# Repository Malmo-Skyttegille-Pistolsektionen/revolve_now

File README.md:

<h1></h1>

Software for running timed shooting programs on a rotating target system, built
by and for Malmö Skyttegille Pistolsektionen.

An ESP32-S3 board turns the targets face-on and edge-on to a shooting program
and plays the spoken range commands over an amplifier. A React web app — served
by the board itself over WiFi — starts and stops programs, follows the run live
over Server-Sent Events, and manages the stored programs and audio.

## ⚠️ SAFETY WARNING — READ BEFORE INSTALLING OR OPERATING

**This device moves steel on a live firing range, and it moves it on a timer.**
A target turns because a program said it was time, not because it can see who
is in front of it. It has no idea anyone is downrange.

- **The range's own safety rules and range commands govern the line. This
  software governs nothing.** A program running is not a range that is hot; a
  program stopped is not a range that is safe.
- **NEVER go downrange because the web app says the run has finished.** Confirm
  a cease-fire the way your range already requires — verbally, with firearms
  cleared and benched.
- **NEVER leave the device powered while people are forward of the firing
  line** unless your club has decided that is safe and knows what the targets
  do at power-up.
- **A target turning can injure somebody standing next to it.** Keep clear of
  the mechanism whenever the device is powered.

The targets rest **shown** at boot, deliberately: a target that turns of its own
accord when a board is powered is the failure this project is most concerned
with. That resting state can be changed to suit a target system wired the other
way round, but only over a USB cable, never from the web app — see
[Expert mode](https://malmo-skyttegille-pistolsektionen.github.io/revolve_now/expert-mode/).

**Do not rely on this software to protect anyone.** It is a convenience for
running programs, not a safety device, and it has no interlock, no sensor, and
no way to know where people are.

**LIABILITY DISCLAIMER:** This project is provided as-is with absolutely no
warranty of any kind. The author(s) accept no responsibility or liability for
any injury, damage, or loss resulting from building, installing, modifying, or
operating this system. You build and use it entirely at your own risk.

---

## Documentation

Everything an operator needs is on the documentation site, in English and
Swedish (the language menu in the header switches):

- **[Operator documentation](https://malmo-skyttegille-pistolsektionen.github.io/revolve_now/)**
  — wiring, connecting, running a program, settings, and what the status LED is
  telling you. This is the one to send a club member.
- **[Program editor](https://malmo-skyttegille-pistolsektionen.github.io/revolve_now/editor/)**
  — write and edit programs in a browser with **no device attached**, then
  download the file or open a pull request against this repository. Also useful
  for reading a shipped program without a board in front of you.
- **[Hardware and wiring](https://malmo-skyttegille-pistolsektionen.github.io/revolve_now/hardware/)**
  — what a target system has to do to work, the DB9 pinout, and the transistor
  that does the switching.

## Installing

Releases ship a pre-built firmware image; you do not need a toolchain to put it
on a board. See
[Connecting](https://malmo-skyttegille-pistolsektionen.github.io/revolve_now/connecting/)
for getting the device onto your network afterwards, and
[Settings](https://malmo-skyttegille-pistolsektionen.github.io/revolve_now/settings/)
for adapting a stock image to your own board — the target pin, its polarity,
the audio and LED pins and the device's name are all configurable on the
device, without rebuilding it.

## Target systems

- **[Eigenbrod TP2](https://eigenbrod-schiessanlagen.de/en/products?tx_produkt_produkte%5Baction%5D=show&tx_produkt_produkte%5BL%5D=2&tx_produkt_produkte%5Bprodukt%5D=319&cHash=942340d5971be0a0ac3d26ff3c257c0b)**
  — what this was built against and what it runs on.

Nothing in the firmware is specific to that system. The board speaks no
proprietary protocol to the targets: it closes and opens **one circuit**, and
the target system's own electronics do the rest. Any system driven the same way
should work.

## Layout

| Directory | Holds |
|---|---|
| [`contracts/`](contracts/README.md) | The canonical API contract: OpenAPI for REST v2, AsyncAPI for SSE v2, the program schema |
| [`firmware/`](firmware/README.md) | The ESP-IDF firmware: target IO, audio, storage, REST + SSE server |
| [`webapp/`](webapp/README.md) | The React front end, embedded in the firmware's application image |
| [`resources/`](resources/README.md) | Shipped programs and audio clips flashed onto the device |
| [`hardware/enclosure/`](hardware/enclosure/README.md) | A 3D-printable box for the rev 2 main board |
| [`docs/`](docs/) | The [decision log](docs/DECISIONS.md), [how releases are cut](docs/RELEASING.md), and the source of the documentation site |

## Contributing

Building, flashing, running it without a device, and the coding standards are
in [`CONTRIBUTING.md`](CONTRIBUTING.md).

## License

MIT — see [`LICENSE`](LICENSE). It covers everything here except the vendored
libraries under `firmware/lib/`, which keep their own.

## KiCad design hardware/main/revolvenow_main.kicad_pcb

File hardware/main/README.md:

# Main board

The Revolve Now main board, rev 2. An ESP32-S3-WROOM-1 (`U1`) drives sixteen
opto-isolated target outputs, reads two opto-isolated trigger inputs, talks to
the network over WiFi or a W5500 Ethernet controller (`U10`), and plays the
range commands through a PCM5102A DAC (`U2`). One WS2812B (`D8`) is the status
LED. 100 × 100 mm, two copper layers.

## Connectors

| Ref | Part | Role |
|---|---|---|
| `J1`, `J2`, `J6`, `J8` | RJ45 | Target outputs Turn 0–3, 4–7, 8–11 and 12–15, through the LTV-847 optocouplers `U4`, `U5`, `U7` and `U8` |
| `J3` | RJ45 | Trigger inputs through the LTV-847 `U3`: pins 1–2 for a 5 V signal, pins 3–6 for 12 V |
| `J4` | USB-C | 5 V power, and the ESP32-S3's native USB (GPIO19/20) behind the USBLC6-2SC6 `U12` |
| `J5` | 1×3 pin header | UART0: RX, GND, TX |
| `J7` | 3.5 mm jack (PJ-320A) | Line out from the DAC |
| `J9` | 2×3 pin header | Jumper that puts GPIO4 on the status LED data (pins 1–2), trigger 0 (3–4) or trigger 1 (5–6) |
| `U11` | RJ45 with magnetics (J0026D21BNL) | Ethernet, from the W5500 |

Each output RJ45 carries four outputs, one per twisted pair, each the
transistor side of one optocoupler channel with the collector on the odd pin:

| Pins | Output |
|---|---|
| 1–2 | first (Turn 0, 4, 8, 12) |
| 3–6 | second |
| 4–5 | third |
| 7–8 | fourth (Turn 3, 7, 11, 15) |

The two buttons are `SW2` (FLASH, on GPIO0) and `SW3` (RESET, on EN).

## Files

| Path | What it is |
|---|---|
| `revolvenow_main.kicad_pro` | The KiCad project. Open this one, in KiCad 10 |
| `revolvenow_main.kicad_sch` | Root schematic, with one sheet per function: ESP, Power, USB, Network, Audio, Output, Trigger, LED |
| `buttons.kicad_sch`, `flash.kicad_sch`, `temperature.kicad_sch` | Sheets no longer in the hierarchy |
| `revolvenow_main.kicad_pcb` | The board |
| `fab/rev2/` | What was sent to the fab, described in the [hardware README](../README.md#fabrication-output) |

Footprints from the shared library come from [`../lib/`](../lib/) through
`fp-lib-table`.

Open items in the design are tracked in the
[rev 2 review on #436](https://github.com/Malmo-Skyttegille-Pistolsektionen/revolve_now/pull/436#issuecomment-6858836932).

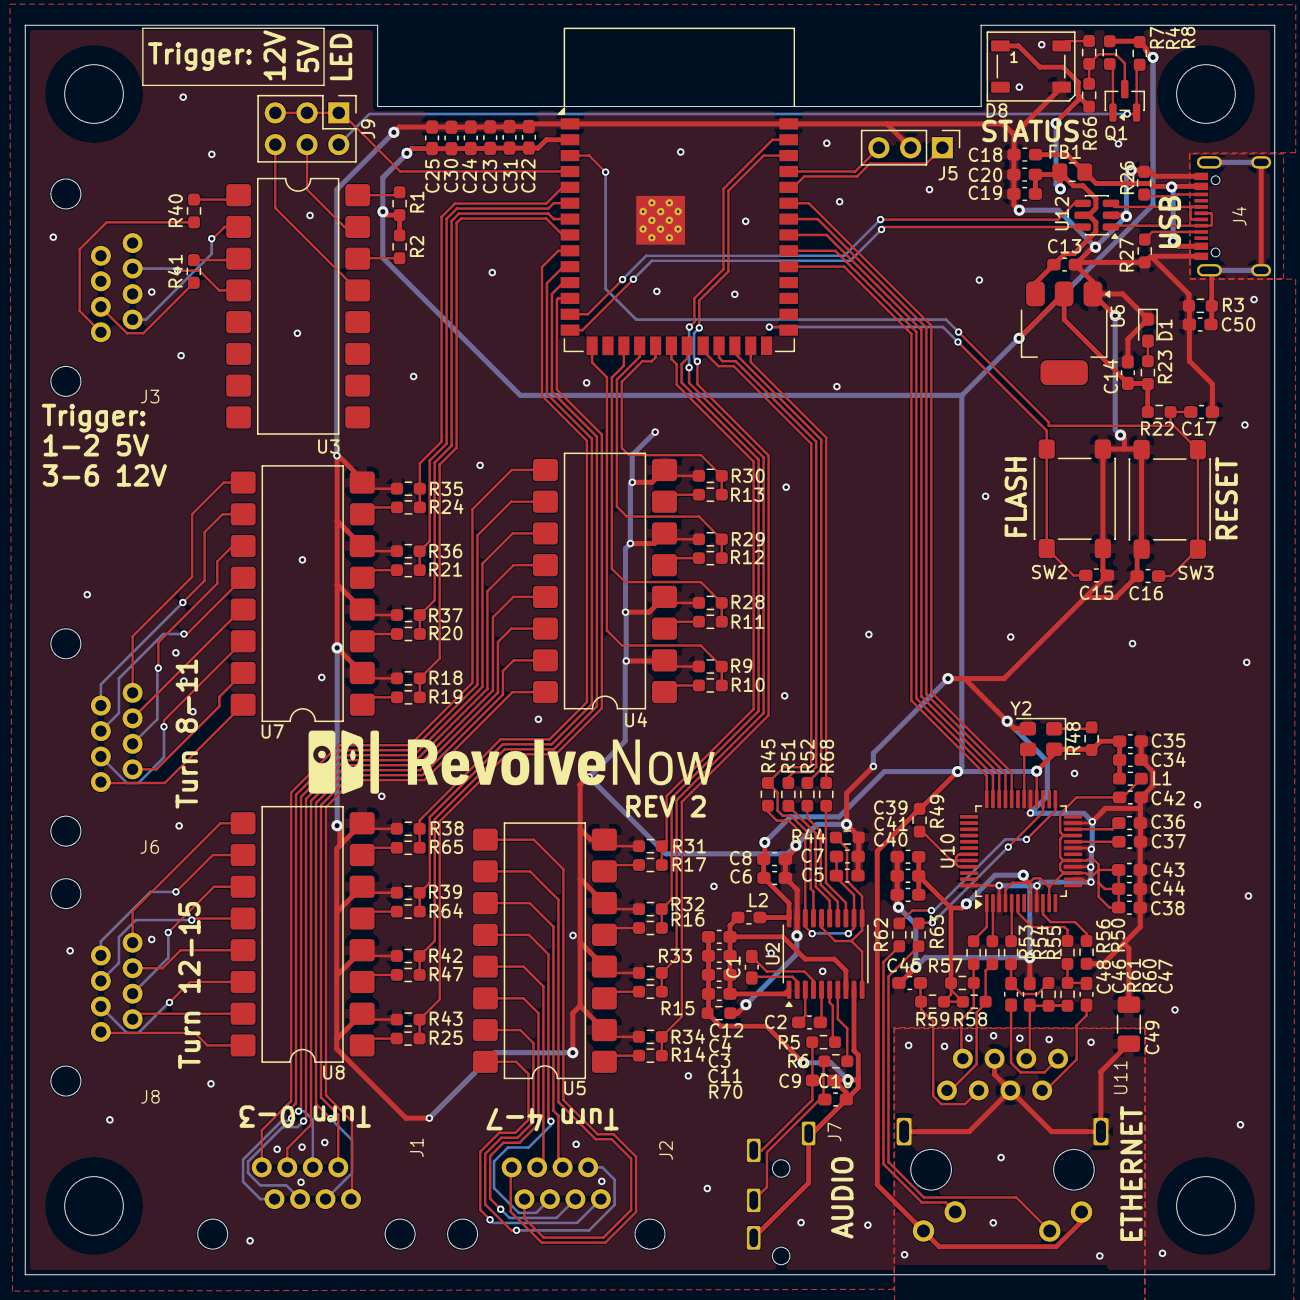
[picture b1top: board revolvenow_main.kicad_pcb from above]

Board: 2 copper layers, 100.0 x 100.0 mm, 139 parts (0 on the bottom side), 143 nets.

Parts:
C1, C2: 2.2uF; C_0603_1608Metric_Pad1.08x0.95mm_HandSolder
C3, C4, C5, C6: 0.1uF; C_0603_1608Metric_Pad1.08x0.95mm_HandSolder
C7, C8, C11, C12, C13, C30, C31, C35, C44: 10uF; C_0603_1608Metric_Pad1.08x0.95mm_HandSolder
C9, C10: 2.2nF; C_0603_1608Metric_Pad1.08x0.95mm_HandSolder
C14: 22uF; C_0603_1608Metric_Pad1.08x0.95mm_HandSolder
C15, C16: C; C_0603_1608Metric_Pad1.08x0.95mm_HandSolder
C17: 1uF; C_0603_1608Metric_Pad1.08x0.95mm_HandSolder
C18, C36, C46: 10nF; C_0603_1608Metric_Pad1.08x0.95mm_HandSolder
C19, C22, C23, C24, C25, C34, C38, C39, C40, C41, C42, C43: 100nF; C_0603_1608Metric_Pad1.08x0.95mm_HandSolder
C20, C37: 4.7uF; C_0603_1608Metric_Pad1.08x0.95mm_HandSolder
C45: 22nF; C_0603_1608Metric_Pad1.08x0.95mm_HandSolder
C47, C48: 6.8nF; C_0603_1608Metric_Pad1.08x0.95mm_HandSolder
C49: 1nF/2kV; C_1206_3216Metric_Pad1.33x1.80mm_HandSolder
C50: 1nF; C_0603_1608Metric_Pad1.08x0.95mm_HandSolder
D1: LED; LED_0603_1608Metric_Pad1.05x0.95mm_HandSolder
D8: WS2812B; LED_WS2812B_PLCC4_5.0x5.0mm_P3.2mm
FB1: FerriteBead; R_0805_2012Metric_Pad1.20x1.40mm_HandSolder
J1, J2, J3, J6, J8: RJ45
J4: USB_C_Receptacle_USB2.0_16P; USB Type-C-02
J5: Conn_01x03_Pin; PinHeader_1x03_P2.54mm_Vertical
J7: AudioJack4; AudioJack PJ-320A
J9: Conn_02x03_Odd_Even; PinHeader_2x03_P2.54mm_Vertical
L1, L2: L; L_0603_1608Metric_Pad1.05x0.95mm_HandSolder
Q1: LGE2300; SOT-23
R1, R2, R9, R18, R22, R28, R29, R30, R31, R32, R33, R34, R35, R36, R37, R38, R39, R42, R43, R44, R45: 10K; R_0603_1608Metric_Pad0.98x0.95mm_HandSolder
R3: 1M; R_0603_1608Metric_Pad0.98x0.95mm_HandSolder
R4, R7: 0; R_0603_1608Metric_Pad0.98x0.95mm_HandSolder
R5, R6: 470R; R_0603_1608Metric_Pad0.98x0.95mm_HandSolder
R8, R48, R49, R66: 10k; R_0603_1608Metric_Pad0.98x0.95mm_HandSolder
R10, R11, R12, R13, R14, R15, R16, R17, R19, R20, R21, R24, R25, R47, R64, R65: 165R; R_0603_1608Metric_Pad0.98x0.95mm_HandSolder
R23: R; R_0603_1608Metric_Pad0.98x0.95mm_HandSolder
R26, R27: 5.1K; R_0603_1608Metric_Pad0.98x0.95mm_HandSolder
R40: 750R; R_0603_1608Metric_Pad0.98x0.95mm_HandSolder
R41: 2.2k; R_0603_1608Metric_Pad0.98x0.95mm_HandSolder
R50: 12.4K; R_0603_1608Metric_Pad0.98x0.95mm_HandSolder
R51, R52, R68: 22R; R_0603_1608Metric_Pad0.98x0.95mm_HandSolder
R53, R54, R55, R56: 33R; R_0603_1608Metric_Pad0.98x0.95mm_HandSolder
R57, R58, R60, R61: 49R9; R_0603_1608Metric_Pad0.98x0.95mm_HandSolder
R59: 10R; R_0603_1608Metric_Pad0.98x0.95mm_HandSolder
R62, R63: 330R; R_0603_1608Metric_Pad0.98x0.95mm_HandSolder
R70: 0R; R_0603_1608Metric_Pad0.98x0.95mm_HandSolder
SW2, SW3: SW_Push; SW_SPST_PTS645Sx43SMTR92
U1: ESP32-S3-WROOM-1
U2: PCM5102A; TSSOP-20_4.4x6.5mm_P0.65mm
U3, U4, U5, U7, U8: LTV-847S; SMDIP-16_W9.53mm
U6: AMS1117-3.3; SOT-223
U10: W5500; LQFP-48_7x7mm_P0.5mm
U11: J0026D21BNL; RJ45_PulseJack_MechB
U12: USBLC6-2SC6; SOT-23-6
Y2: 25MHz; Oscillator_SMD_Abracon_ASE-4Pin_3.2x2.5mm

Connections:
+3.3V: C6.1, C8.1, C14.1, C22.1, C23.1, C24.1, C25.1, C30.1, C31.1, C34.1, C35.1, L1.1, L2.1, R1.1, R2.1, R4.1, R8.1, R22.1, R23.1, R48.1, R49.1, U1.2 (3V3), U2.20 (DVDD), U6.2 (VO), U10.28 (VDD), U11.9, U11.12, Y2.4 (Vdd)
+3.3VA_Audio: C3.1, C4.1, C11.1, C12.1, L2.2, U2.1 (CPVDD), U2.8 (AVDD)
+3.3VA_Ethernet: C38.1, C39.1, C40.1, C41.1, C42.1, C43.1, C44.1, L1.2, R57.1, R58.1, R59.1, U10.4 (AVDD), U10.8 (AVDD), U10.11 (AVDD), U10.15 (AVDD), U10.17 (AVDD), U10.21 (AVDD)
+5V: C13.1, C19.1, C20.1, D8.1 (VDD), FB1.2, R66.1, U6.3 (VI), U12.5 (VBUS)
/Audio/BCK: R68.1, U1.25 (IO48)
/Audio/Mute: R45.1, U1.22 (IO14), U2.17 (XSMT)
/Audio/SD: R52.1, U1.24 (IO47)
/Audio/WS: R51.1, U1.23 (IO21)
/ESP/INT_NET: U1.31 (IO38), U10.36 (~INT)
/ESP/LED_DIN: J9.2, Q1.2 (S), R8.2
/ESP/SPI_CLK: U1.34 (IO41), U10.33 (SCLK)
/ESP/SPI_CS_NET: U1.35 (IO42), U10.32 (~SCS)
/ESP/SPI_MISO: U1.33 (IO40), U10.34 (MISO)
/ESP/SPI_MOSI: U1.32 (IO39), U10.35 (MOSI)
/ESP/Trigger0: J9.4, U3.15
/ESP/Trigger1: J9.6, U3.13
/ESP/Turn0: R9.1, R10.1, U1.15 (IO3)
/ESP/Turn1: R11.1, R28.1, U1.17 (IO9)
/ESP/Turn2: R12.1, R29.1, U1.18 (IO10)
/ESP/Turn3: R13.1, R30.1, U1.19 (IO11)
/ESP/Turn4: R14.1, R34.1, U1.38 (IO2)
/ESP/Turn5: R15.1, R33.1, U1.39 (IO1)
/ESP/Turn6: R16.1, R32.1, U1.21 (IO13)
/ESP/Turn7: R17.1, R31.1, U1.20 (IO12)
/ESP/Turn8: R18.1, R19.1, U1.8 (IO15)
/ESP/Turn9: R20.1, R37.1, U1.7 (IO7)
/ESP/Turn10: R21.1, R36.1, U1.6 (IO6)
/ESP/Turn11: R24.1, R35.1, U1.5 (IO5)
/ESP/Turn12: R25.1, R43.1, U1.12 (IO8)
/ESP/Turn13: R42.1, R47.1, U1.11 (IO18)
/ESP/Turn14: R39.1, R64.1, U1.10 (IO17)
/ESP/Turn15: R38.1, R65.1, U1.9 (IO16)
/ESP/UART_RX: J5.1, U1.36 (RXD0)
/ESP/UART_TX: J5.3, U1.37 (TXD0)
/ESP/USB_D+: U1.14 (USB_D+), U12.6 (I/O1)
/ESP/USB_D-: U1.13 (USB_D-), U12.4 (I/O2)
CGND: C49.2, U11.4 (CHS_GND), U11.5 (CHS_GND), U11.SH
GND: C5.1, C6.2, C7.1, C8.2, C13.2, C14.2, C15.1, C16.1, C17.2, C18.2, C19.2, C20.2, C22.2, C23.2, C24.2, C25.2, C30.2, C31.2, C34.2, C35.2, C36.2, C37.2, C38.2, C39.2, C40.2, C41.2, C42.2, C43.2, C44.2, C45.2, C46.2, C49.1, C50.1, D1.1 (K), D8.3 (VSS), J4.A1 (GND), J4.B1 (GND), J5.2, R3.2, R9.2, R18.2, R26.2, R27.2, R28.2, R29.2, R30.2, R31.2, R32.2, R33.2, R34.2, R35.2, R36.2, R37.2, R38.2, R39.2, R42.2, R43.2, R44.2, R50.2, R70.1, SW2.1, SW3.2, U1.1 (GND), U1.40 (GND), U1.41 (GND), U2.19 (DGND), U4.2, U4.4, U4.6, U4.8, U5.2, U5.4, U5.6, U5.8, U6.1 (GND), U7.2, U7.4, U7.6, U7.8, U8.2, U8.4, U8.6, U8.8, U10.3 (AGND), U10.9 (AGND), U10.14 (AGND), U10.16 (AGND), U10.19 (AGND), U10.23 (RSVD), U10.29 (GND), U10.48 (AGND), U12.2 (GND), Y2.2 (GND)
GNDA: C3.2, C4.2, C9.2, C10.2, C11.2, C12.2, J7.R2, J7.S, R70.2, U2.9 (AGND)
unnamed: C9.1, J7.T, R5.2
unnamed: C10.1, J7.R1, R6.2
unnamed: C47.1, R56.2, R60.1
unnamed: C48.1, R55.2, R61.1
unnamed: D1.2 (A), R23.2
unnamed: D8.4 (DIN), R7.2
unnamed: J1.1, U4.16
unnamed: J1.2, U4.15
unnamed: J1.3, U4.14
unnamed: J1.4, U4.11
unnamed: J1.5, U4.12
unnamed: J1.6, U4.13
unnamed: J1.7, U4.10
unnamed: J1.8, U4.9
unnamed: J2.1, U5.16
unnamed: J2.2, U5.15
unnamed: J2.3, U5.14
unnamed: J2.4, U5.11
unnamed: J2.5, U5.12
unnamed: J2.6, U5.13
unnamed: J2.7, U5.10
unnamed: J2.8, U5.9
unnamed: J3.1, R40.1
unnamed: J3.2, U3.2
unnamed: J3.3, R41.1
unnamed: J3.6, U3.4
unnamed: J4.A5 (CC1), R27.1
unnamed: J4.B5 (CC2), R26.1
unnamed: J4.A6 (D+), J4.B6 (D+), U12.3 (I/O2)
unnamed: J4.A7 (D-), J4.B7 (D-), U12.1 (I/O1)
unnamed: C50.2, J4.S1 (SHIELD), R3.1
unnamed: J6.1, U7.16
unnamed: J6.2, U7.15
unnamed: J6.3, U7.14
unnamed: J6.4, U7.11
unnamed: J6.5, U7.12
unnamed: J6.6, U7.13
unnamed: J6.7, U7.10
unnamed: J6.8, U7.9
unnamed: J8.1, U8.16
unnamed: J8.2, U8.15
unnamed: J8.3, U8.14
unnamed: J8.4, U8.11
unnamed: J8.5, U8.12
unnamed: J8.6, U8.13
unnamed: J8.7, U8.10
unnamed: J8.8, U8.9
unnamed: J9.1, J9.3, J9.5, U1.4 (IO4)
unnamed: Q1.3 (D), R7.1, R66.2
unnamed: Q1.1 (G), R4.2
unnamed: R1.2, U3.16
unnamed: R2.2, U3.14
unnamed: R10.2, U4.1
unnamed: R11.2, U4.3
unnamed: R12.2, U4.5
unnamed: R13.2, U4.7
unnamed: R14.2, U5.1
unnamed: R15.2, U5.3
unnamed: R16.2, U5.5
unnamed: R17.2, U5.7
unnamed: R19.2, U7.1
unnamed: R20.2, U7.3
unnamed: R21.2, U7.5
unnamed: R24.2, U7.7
unnamed: R25.2, U8.1
unnamed: R40.2, U3.1
unnamed: R41.2, U3.3
unnamed: R47.2, U8.3
unnamed: R62.1, U11.10
unnamed: R63.1, U11.11
unnamed: R64.2, U8.5
unnamed: R65.2, U8.7
unnamed: C16.2, C17.1, R22.2, SW3.1, U1.3 (EN)
unnamed: C15.2, SW2.2, U1.27 (IO0)
unnamed: R68.2, U2.13 (BCK)
unnamed: C1.2, U2.4 (CAPM)
unnamed: C1.1, U2.2 (CAPP)
unnamed: C2.2, U2.3 (CPGND)
unnamed: R44.1, U2.10 (DEMP), U2.11 (FLT), U2.16 (FMT)
unnamed: R52.2, U2.14 (DIN)
unnamed: C5.2, C7.2, R45.2, U2.12 (SCK), U2.18 (LDOO)
unnamed: R51.2, U2.15 (LRCK)
unnamed: R5.1, U2.6 (OUTL)
unnamed: R6.1, U2.7 (OUTR)
unnamed: C2.1, U2.5 (VNEG)
unnamed: C36.1, U10.22 (1V2O)
unnamed: R63.2, U10.27 (ACTLED)
unnamed: R50.1, U10.10 (EXRES1)
unnamed: R62.2, U10.25 (LINKLED)
unnamed: R49.2, U10.43 (PMODE2), U10.44 (PMODE1), U10.45 (PMODE0)
unnamed: R55.1, U10.5 (RXN)
unnamed: R56.1, U10.6 (RXP)
unnamed: C37.1, U10.20 (TOCAP)
unnamed: R53.1, U10.1 (TXN)
unnamed: R54.1, U10.2 (TXP)
unnamed: U10.30 (XI/CLKIN), Y2.3 (OUT)
unnamed: C46.1, R60.2, R61.2, U11.6 (RCT)
unnamed: C47.2, U11.7 (RD+)
unnamed: C48.2, U11.8 (RD-)
unnamed: C45.1, R59.2, U11.3 (TCT)
unnamed: R54.2, R58.2, U11.1 (TD+)
unnamed: R53.2, R57.2, U11.2 (TD-)
unnamed: R48.2, Y2.1 (EN)
VBUS: C18.1, FB1.1, J4.A4 (VBUS), J4.B4 (VBUS)

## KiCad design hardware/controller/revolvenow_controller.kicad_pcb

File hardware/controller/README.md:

# Controller board

The Revolve Now controller board (the relay box), rev 2. It has no
microcontroller: eight LGE2300 N-channel MOSFETs (`Q1`–`Q8`) switch the target
outputs low, driven from the inputs on `J9`. The board is two halves, labelled
**1–2** and **3–4** on the silkscreen, each with its own USB-C power input,
output RJ45 and output header. 95 × 50 mm, two copper layers.

## Connectors

| Ref | Part | Role |
|---|---|---|
| `J3` | RJ45 | Outputs of half 1–2: the drains of `Q1`–`Q4` on pins 1, 3, 5, 7, ground on 2, 4, 6, 8 |
| `J5` | RJ45 | Outputs of half 3–4, the same way, from `Q5`–`Q8` |
| `J4`, `J6` | 1×6 pin header | +5 V, GND and the four outputs of half 1–2 and 3–4 |
| `J7`, `J8` | USB-C | 5 V power for half 1–2 and 3–4. Power only: the data lines are not connected |
| `J9` | RJ45 | Manual remote control: +5 V on pins 1, 3, 5, 7, MOSFET gates on 2, 4, 6, 8 |
| `J1`, `J2` | 2×2 pin header | Jumpers that join the +5 V (`J1`) and the GND (`J2`) of the two halves. `R1` and `R2`, 0 Ω and not fitted, do the same |

Each `J9` pair drives two MOSFETs, so one input switches two outputs:

| `J9` pins | MOSFETs | Outputs |
|---|---|---|
| 1–2 | `Q1`, `Q3` | `J3` pins 1 and 5 |
| 3–4 | `Q2`, `Q4` | `J3` pins 3 and 7 |
| 5–6 | `Q5`, `Q7` | `J5` pins 1 and 5 |
| 7–8 | `Q6`, `Q8` | `J5` pins 3 and 7 |

## Files

| Path | What it is |
|---|---|
| `revolvenow_controller.kicad_pro` | The KiCad project. Open this one, in KiCad 10 |
| `revolvenow_controller.kicad_sch` | Root schematic: the Controller sheet, and `power1.kicad_sch` and `output1.kicad_sch` each used twice, once per half |
| `revolvenow_controller.kicad_pcb` | The board |
| `fab/rev2/` | What was sent to the fab, described in the [hardware README](../README.md#fabrication-output) |

Footprints from the shared library come from [`../lib/`](../lib/) through
`fp-lib-table`.

Open items in the design are tracked in the
[rev 2 review on #603](https://github.com/Malmo-Skyttegille-Pistolsektionen/revolve_now/pull/603#issuecomment-6858837484).

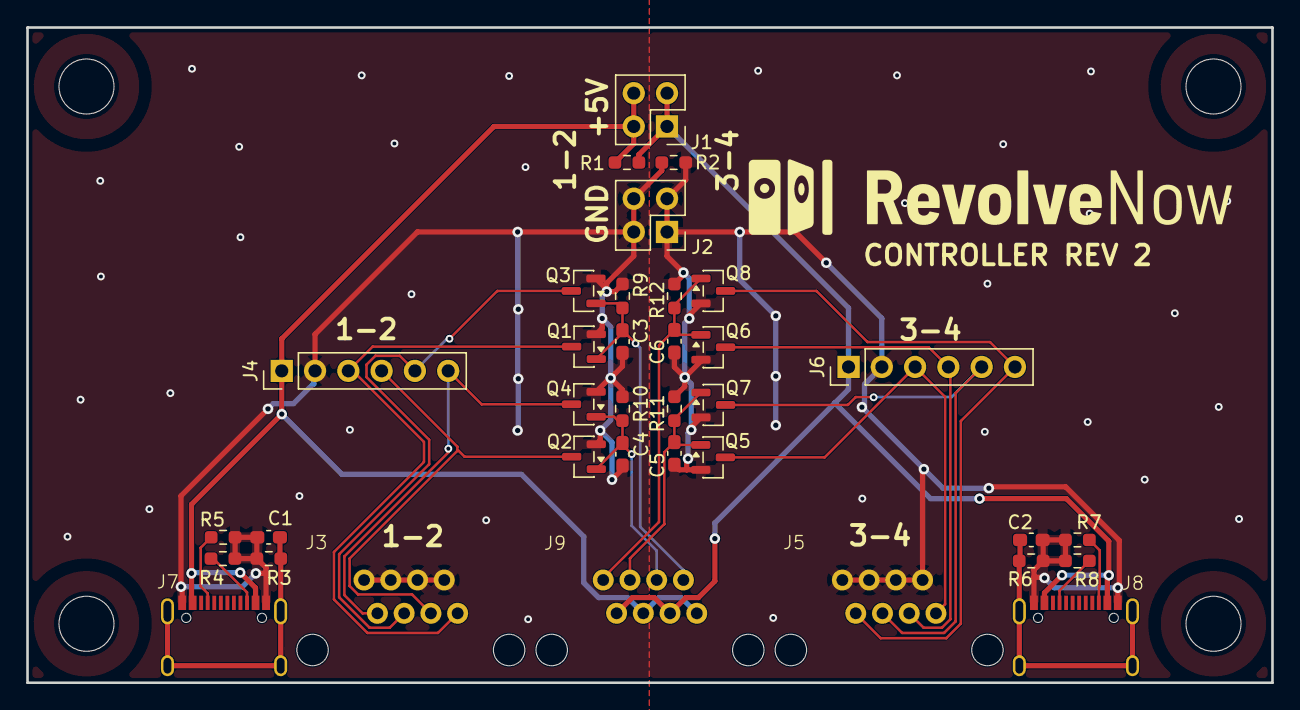
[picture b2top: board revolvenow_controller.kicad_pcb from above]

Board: 2 copper layers, 95.0 x 50.0 mm, 35 parts (0 on the bottom side), 21 nets.

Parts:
C1, C2: 1nF; C_0603_1608Metric_Pad1.08x0.95mm_HandSolder
C3, C4, C5, C6: 100n; C_0603_1608Metric_Pad1.08x0.95mm_HandSolder
J1, J2: Conn_02x02_Top_Bottom; PinHeader_2x02_P2.54mm_Vertical
J3, J5, J9: RJ45
J4, J6: Conn_01x06_Pin; PinHeader_1x06_P2.54mm_Vertical
J7, J8: USB_C_Receptacle_USB2.0_16P; USB Type-C-02
Q1, Q2, Q3, Q4, Q5, Q6, Q7, Q8: LGE2300; SOT-23
R1, R2: 0R; R_0603_1608Metric_Pad0.98x0.95mm_HandSolder
R3, R6: 1M; R_0603_1608Metric_Pad0.98x0.95mm_HandSolder
R4, R5, R7, R8: 5.1K; R_0603_1608Metric_Pad0.98x0.95mm_HandSolder
R9, R10, R11, R12: 10k; R_0603_1608Metric_Pad0.98x0.95mm_HandSolder

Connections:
+5V(1): J1.2, J1.4, J4.1, J7.A4 (VBUS), J7.B4 (VBUS), J9.1, J9.5, R1.1
+5V(2): J1.1, J1.3, J6.1, J8.A4 (VBUS), J8.B4 (VBUS), J9.3, J9.7, R1.2
/Controller/Output1-1: J3.1, J4.3, Q1.3 (D)
/Controller/Output1-2: J3.3, J4.4, Q2.3 (D)
/Controller/Output1-3: J3.5, J4.5, Q3.3 (D)
/Controller/Output1-4: J3.7, J4.6, Q4.3 (D)
/Controller/Output2-1: J5.1, J6.3, Q5.3 (D)
/Controller/Output2-2: J5.3, J6.4, Q6.3 (D)
/Controller/Output2-3: J5.5, J6.5, Q7.3 (D)
/Controller/Output2-4: J5.7, J6.6, Q8.3 (D)
GND(1): C1.2, C3.2, C4.2, J2.2, J2.4, J3.2, J3.4, J3.6, J3.8, J4.2, J7.A1 (GND), J7.B1 (GND), Q1.2 (S), Q2.2 (S), Q3.2 (S), Q4.2 (S), R2.2, R3.2, R4.2, R5.2, R9.1, R10.1
GND(2): C2.2, C5.2, C6.1, J2.1, J2.3, J5.2, J5.4, J5.6, J5.8, J6.2, J8.A1 (GND), J8.B1 (GND), Q5.2 (S), Q6.2 (S), Q7.2 (S), Q8.2 (S), R2.1, R6.2, R7.2, R8.2, R11.1, R12.1
unnamed: J7.A5 (CC1), R5.1
unnamed: J7.B5 (CC2), R4.1
unnamed: J8.A5 (CC1), R8.1
unnamed: J8.B5 (CC2), R7.1
unnamed: C3.1, J9.2, Q1.1 (G), Q3.1 (G), R9.2
unnamed: C4.1, J9.4, Q2.1 (G), Q4.1 (G), R10.2
unnamed: C5.1, J9.6, Q5.1 (G), Q7.1 (G), R11.2
unnamed: C6.2, J9.8, Q6.1 (G), Q8.1 (G), R12.2
SH: C1.1, C2.1, J7.SH (SHIELD), J8.SH (SHIELD), R3.1, R6.1
